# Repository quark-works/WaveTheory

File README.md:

# WaveTheroy

Wireless column staggered PCB compatible with GH60 tray mount cases.

## Features
- 12x4 column staggered board with space for two optional encoders.
- Powered by a e73-2G4M08S1C module, nrf52840 and running ZMK. Firmware available here: [wavetheory-zmk-config](https://github.com/quark-works/wavetheroy-zmk-config).
- Board is in Full HV mode, with a battery of 110 mAh the expected life is around 1 month.
- Has space for a nice!view to show information regarding layers, battery, etc.
- Compatible with GH60 tray mount cases (as pictured).

## More pictures

## This board was prototyped and working, but there are still things to do
- [ ] Add configuration in the firmware for the two encoders.
- [ ] Add configuration in the firmware for the missing compatible layouts.
- [ ] Provide a BOM and POS file for assembly.
- [ ] Fix a bodge wire in the prototype.

## Acknowledgements

Project based off from [Scientist Keyboard](https://github.com/godders/scientist). It uses the same layout based on their reference.

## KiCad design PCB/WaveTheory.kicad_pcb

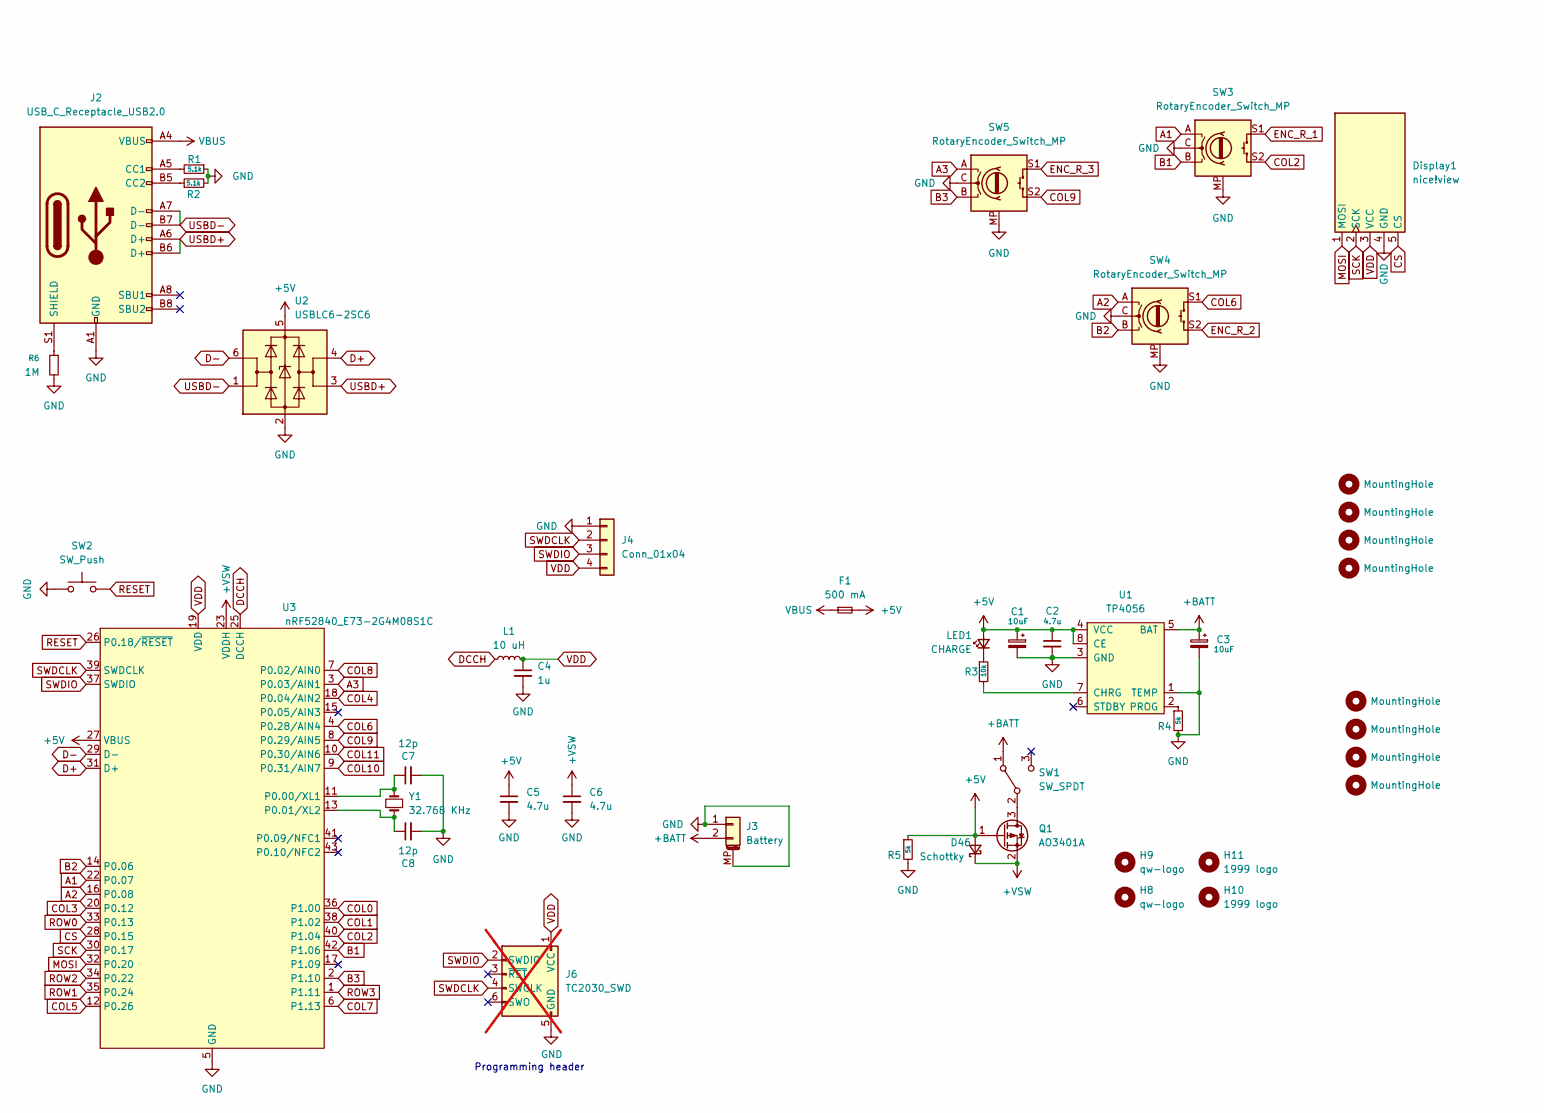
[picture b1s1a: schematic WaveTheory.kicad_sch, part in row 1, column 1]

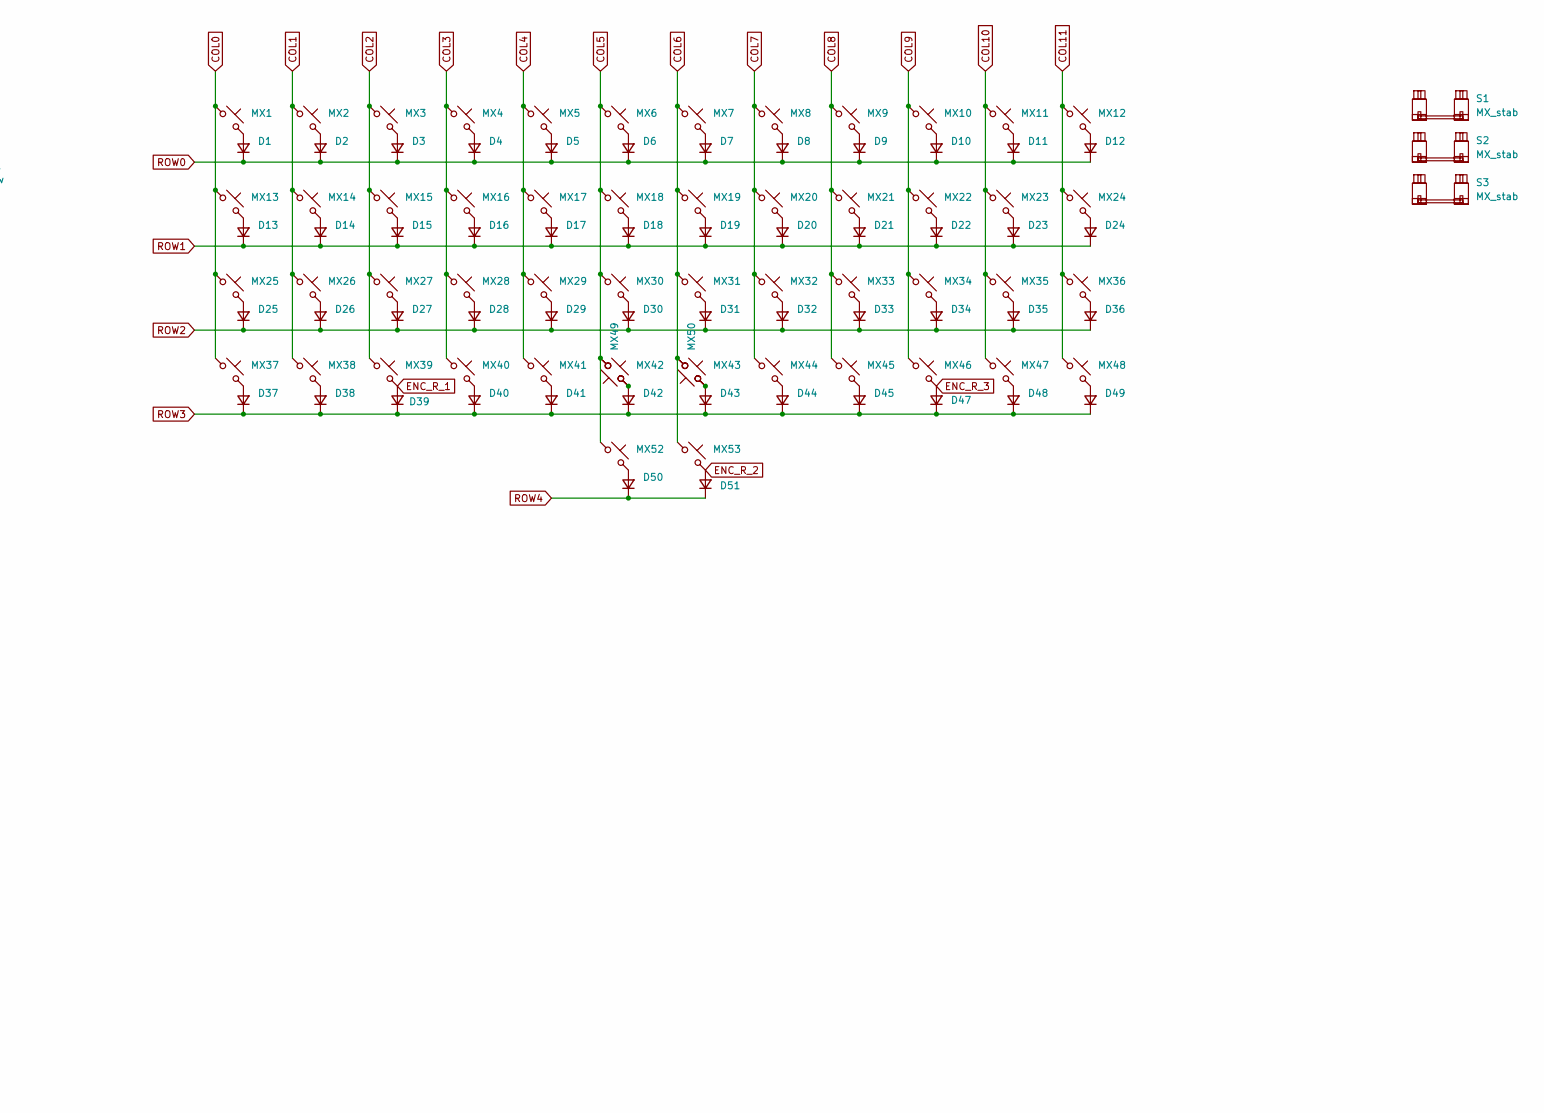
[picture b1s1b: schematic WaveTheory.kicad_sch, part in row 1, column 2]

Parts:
C1, C3: 10uF; CP_EIA-2012-12_Kemet-R
C2, C5, C6: 4.7u; C_0603_1608Metric
C4: 1u; C_0603_1608Metric
C7, C8: 12p; C_0603_1608Metric
D1, D2, D3, D4, D5, D6, D7, D8, D9, D10, D11, D12, D13, D14, D15, D16, D17, D18, D19, D20, D21, D22, D23, D24, D25, D26, D27, D28, D29, D30, D31, D32, D33, D34, D35, D36, D37, D38, D39, D40, D41, D42, D43, D44, D45, D47, D48, D49, D50, D51: 1N4148; CUSTOM D_SOD-123
D46: Schottky; D_0603_1608Metric
Display1: nice!view; nice_view
F1: 500 mA; Fuse_1206_3216Metric
H1, H2, H3, H4: MountingHole; mounting_hole
H5, H6, H7, H12: MountingHole; MountingHole_2.2mm_M2
H8, H9: qw-logo; qw new logo silk + copper sm
H10, H11: 1999 logo; 1999 logo md
J2: USB_C_Receptacle_USB2.0; USB_C_Receptacle_HRO_TYPE-C-31-M-12
J3: Battery; JST_PH_S2B-PH-K_1x02_P2.00mm_Horizontal; LCSC C505023
J4: Conn_01x04; PinHeader_1x04_P2.54mm_Vertical
J6: TC2030_SWD; CON_TC2030_outlined; not fitted
L1: 10 uH; L_0603_1608Metric; LCSC C92982
LED1: CHARGE; LED_0805_2012Metric
MX1, MX2, MX3, MX4, MX5, MX6, MX7, MX8, MX9, MX10, MX11, MX12, MX13, MX14, MX15, MX16, MX17, MX18, MX19, MX20, MX21, MX22, MX23, MX24, MX25, MX26, MX27, MX28, MX29, MX30, MX31, MX32, MX33, MX34, MX35, MX36, MX37, MX38, MX39, MX40, MX41, MX42, MX43, MX44, MX45, MX46, MX47, MX48, MX49, MX50, MX52, MX53: MX_SW_HS; SW_MX_1u
Q1: AO3401A; SOT-23
R1, R2: 5.1k; R_0603_1608Metric
R3: 10k; R_0603_1608Metric
R4, R5: 5k; R_0603_1608Metric
R6: 1M; R_0603_1608Metric
S1, S2, S3: MX_stab; STAB_MX_P_2u
SW1: SW_SPDT; SW_Slide_SPDT_Straight_CK_OS102011MS2Q; LCSC C41430893
SW2: SW_Push; SW_SPST_SKQG_WithStem
SW3, SW4, SW5: RotaryEncoder_Switch_MP; ROT_Alps_EC11E-Switch
U1: TP4056; CustomTP4056; LCSC C16581
U2: USBLC6-2SC6; SOT-23-6
U3: nRF52840_E73-2G4M08S1C; LCSC C356849
Y1: 32.768 KHz; Crystal_SMD_2012-2Pin_2.0x1.2mm; LCSC C55208

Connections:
+5V: C1.1, C2.1, C5.1, D46.2 (A), F1.2, LED1.2 (A), Q1.1 (G), R5.1, U1.4 (VCC), U1.8 (CE), U2.5 (VBUS), U3.27 (VBUS)
+BATT: C3.1, J3.2, SW1.1 (A), U1.5 (BAT)
+VSW: C6.1, D46.1 (K), Q1.2 (S), U3.23 (VDDH)
A1: SW3.A, U3.22 (P0.07)
A2: SW4.A, U3.16 (P0.08)
A3: SW5.A, U3.3 (P0.03/AIN1)
B1: SW3.B, U3.42 (P1.06)
B2: SW4.B, U3.14 (P0.06)
B3: SW5.B, U3.2 (P1.10)
COL0: MX1.2, MX13.2, MX25.2, MX37.2, U3.36 (P1.00)
COL1: MX2.2, MX14.2, MX26.2, MX38.2, U3.38 (P1.02)
COL2: MX3.2, MX15.2, MX27.2, MX39.2, SW3.S2, U3.40 (P1.04)
COL3: MX4.2, MX16.2, MX28.2, MX40.2, U3.20 (P0.12)
COL4: MX5.2, MX17.2, MX29.2, MX41.2, U3.18 (P0.04/AIN2)
COL5: MX6.2, MX18.2, MX30.2, MX42.2, MX49.2, MX52.2, U3.12 (P0.26)
COL6: MX7.2, MX19.2, MX31.2, MX43.2, MX50.2, MX53.2, SW4.S1, U3.4 (P0.28/AIN4)
COL7: MX8.2, MX20.2, MX32.2, MX44.2, U3.6 (P1.13)
COL8: MX9.2, MX21.2, MX33.2, MX45.2, U3.7 (P0.02/AIN0)
COL9: MX10.2, MX22.2, MX34.2, MX46.2, SW5.S2, U3.8 (P0.29/AIN5)
COL10: MX11.2, MX23.2, MX35.2, MX47.2, U3.9 (P0.31/AIN7)
COL11: MX12.2, MX24.2, MX36.2, MX48.2, U3.10 (P0.30/AIN6)
CS: Display1.5 (CS), U3.28 (P0.15)
D+: U2.4 (I/O2), U3.31 (D+)
D-: U2.6 (I/O1), U3.29 (D-)
DCCH: L1.1, U3.25 (DCCH)
ENC_R_1: D39.2 (A), MX39.1, SW3.S1
ENC_R_2: D51.2 (A), MX53.1, SW4.S2
ENC_R_3: D47.2 (A), MX46.1, SW5.S1
GND: C1.2, C2.2, C3.2, C4.2, C5.2, C6.2, C7.2, C8.2, Display1.4 (GND), J2.A1 (GND), J2.A12 (GND), J2.B1 (GND), J2.B12 (GND), J3.1, J3.MP (MountPin), J4.1, J6.5 (GND), R1.1, R2.2, R4.2, R5.2, R6.2, SW2.1, SW3.C, SW3.MP, SW4.C, SW4.MP, SW5.C, SW5.MP, U1.1 (TEMP), U1.3 (GND), U2.2 (GND), U3.5 (GND), U3.21 (GND), U3.24 (GND)
MOSI: Display1.1 (MOSI), U3.32 (P0.20)
unnamed: D1.2 (A), MX1.1
unnamed: D2.2 (A), MX2.1
unnamed: D3.2 (A), MX3.1
unnamed: D4.2 (A), MX4.1
unnamed: D5.2 (A), MX5.1
unnamed: D6.2 (A), MX6.1
unnamed: D7.2 (A), MX7.1
unnamed: D8.2 (A), MX8.1
unnamed: D9.2 (A), MX9.1
unnamed: D10.2 (A), MX10.1
unnamed: D11.2 (A), MX11.1
unnamed: D12.2 (A), MX12.1
unnamed: D13.2 (A), MX13.1
unnamed: D14.2 (A), MX14.1
unnamed: D15.2 (A), MX15.1
unnamed: D16.2 (A), MX16.1
unnamed: D17.2 (A), MX17.1
unnamed: D18.2 (A), MX18.1
unnamed: D19.2 (A), MX19.1
unnamed: D20.2 (A), MX20.1
unnamed: D21.2 (A), MX21.1
unnamed: D22.2 (A), MX22.1
unnamed: D23.2 (A), MX23.1
unnamed: D24.2 (A), MX24.1
unnamed: D25.2 (A), MX25.1
unnamed: D26.2 (A), MX26.1
unnamed: D27.2 (A), MX27.1
unnamed: D28.2 (A), MX28.1
unnamed: D29.2 (A), MX29.1
unnamed: D30.2 (A), MX30.1
unnamed: D31.2 (A), MX31.1
unnamed: D32.2 (A), MX32.1
unnamed: D33.2 (A), MX33.1
unnamed: D34.2 (A), MX34.1
unnamed: D35.2 (A), MX35.1
unnamed: D36.2 (A), MX36.1
unnamed: D37.2 (A), MX37.1
unnamed: D38.2 (A), MX38.1
unnamed: D40.2 (A), MX40.1
unnamed: D41.2 (A), MX41.1
unnamed: D42.2 (A), MX42.1, MX49.1
unnamed: D43.2 (A), MX43.1, MX50.1
unnamed: D44.2 (A), MX44.1
unnamed: D45.2 (A), MX45.1
unnamed: D48.2 (A), MX47.1
unnamed: D49.2 (A), MX48.1
unnamed: D50.2 (A), MX52.1
unnamed: J2.A5 (CC1), R1.2
unnamed: J2.B5 (CC2), R2.1
unnamed: J2.S1 (SHIELD), R6.1
unnamed: LED1.1 (K), R3.1
unnamed: Q1.3 (D), SW1.2 (B)
unnamed: R3.2, U1.7 (CHRG)
unnamed: R4.1, U1.2 (PROG)
unnamed: C7.1, U3.11 (P0.00/XL1), Y1.2
unnamed: C8.1, U3.13 (P0.01/XL2), Y1.1
RESET: SW2.2, U3.26 (P0.18/~RESET)
ROW0: D1.1 (K), D2.1 (K), D3.1 (K), D4.1 (K), D5.1 (K), D6.1 (K), D7.1 (K), D8.1 (K), D9.1 (K), D10.1 (K), D11.1 (K), D12.1 (K), U3.33 (P0.13)
ROW1: D13.1 (K), D14.1 (K), D15.1 (K), D16.1 (K), D17.1 (K), D18.1 (K), D19.1 (K), D20.1 (K), D21.1 (K), D22.1 (K), D23.1 (K), D24.1 (K), U3.35 (P0.24)
ROW2: D25.1 (K), D26.1 (K), D27.1 (K), D28.1 (K), D29.1 (K), D30.1 (K), D31.1 (K), D32.1 (K), D33.1 (K), D34.1 (K), D35.1 (K), D36.1 (K), U3.34 (P0.22)
ROW3: D37.1 (K), D38.1 (K), D39.1 (K), D40.1 (K), D41.1 (K), D42.1 (K), D43.1 (K), D44.1 (K), D45.1 (K), D47.1 (K), D48.1 (K), D49.1 (K), U3.1 (P1.11)
ROW4: D50.1 (K), D51.1 (K)
SCK: Display1.2 (SCK), U3.30 (P0.17)
SWDCLK: J4.2, J6.4 (SWCLK), U3.39 (SWDCLK)
SWDIO: J4.3, J6.2 (SWDIO), U3.37 (SWDIO)
USBD+: J2.A6 (D+), J2.B6 (D+), U2.3 (I/O2)
USBD-: J2.A7 (D-), J2.B7 (D-), U2.1 (I/O1)
VBUS: F1.1, J2.A4 (VBUS), J2.A9 (VBUS), J2.B4 (VBUS), J2.B9 (VBUS)
VDD: C4.1, Display1.3 (VCC), J4.4, J6.1 (VCC), L1.2, U3.19 (VDD)

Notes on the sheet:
Programming header

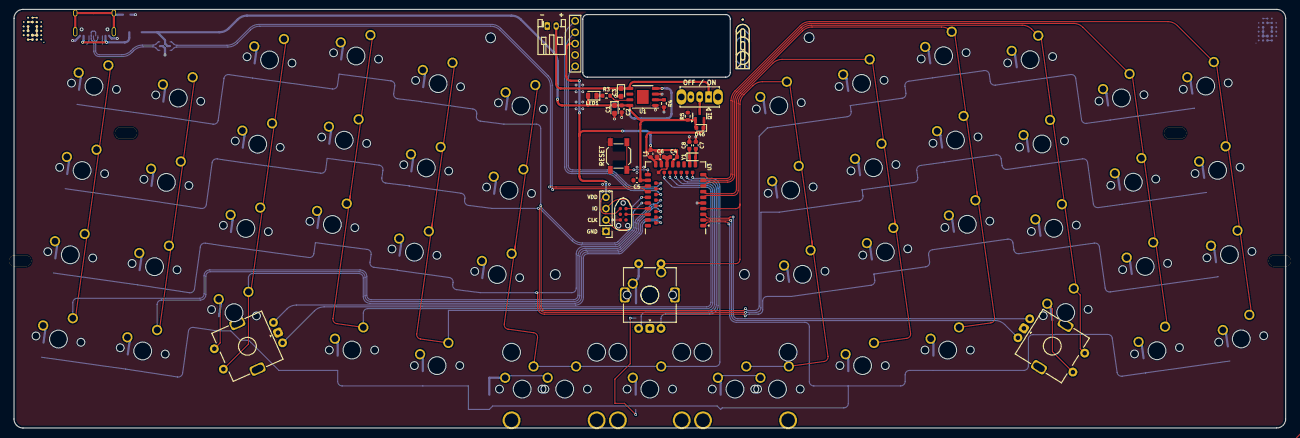
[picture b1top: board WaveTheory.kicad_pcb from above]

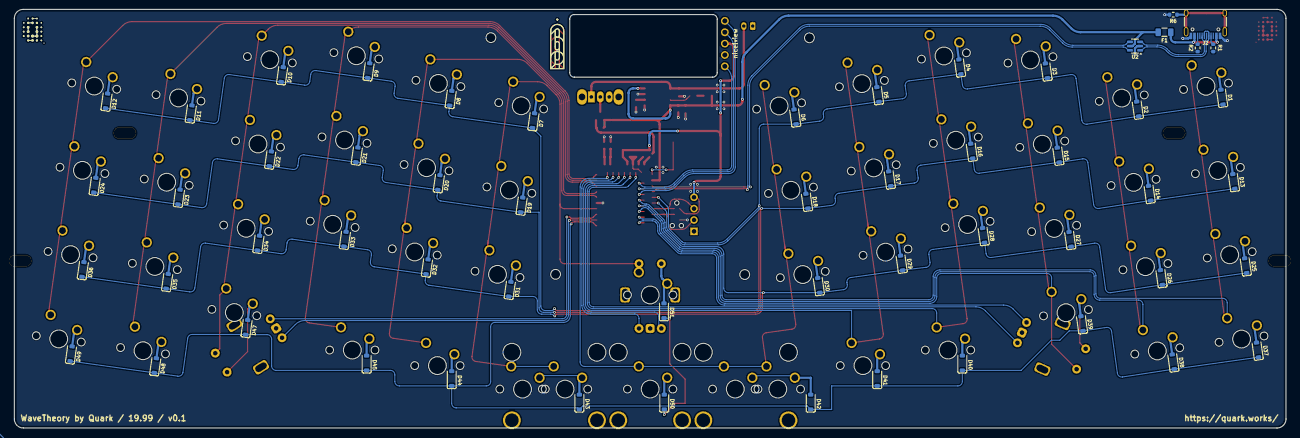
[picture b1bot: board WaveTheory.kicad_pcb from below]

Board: 2 copper layers, 284.6 x 93.7 mm, 150 parts (58 on the bottom side), 99 nets.

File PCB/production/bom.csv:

Designator,Footprint,Quantity,Value,LCSC Part #
"C1, C3",CP_EIA-2012-12_Kemet-R,2,10uF,
"C2, C5, C6",0603,3,4.7u,
C4,0603,1,1u,
"C7, C8",0603,2,12p,
"D1, D10, D11, D12, D13, D14, D15, D16, D17, D18, D19, D2, D20, D21, D22, D23, D24, D25, D26, D27, D28, D29, D3, D30, D31, D32, D33, D34, D35, D36, D37, D38, D39, D4, D40, D41, D42, D43, D44, D45, D47, D48, D49, D5, D50, D51, D6, D7, D8, D9",CUSTOM D_SOD-123,50,1N4148,
D46,0603,1,Schottky,
DISPLAY1,nice_view,1,nice!view,
F1,1206,1,500 mA,
J2,USB_C_Receptacle_HRO_TYPE-C-31-M-12,1,USB_C_Receptacle_USB2.0,
J3,JST_PH_S2B-PH-K_1x02_P2.00mm_Horizontal,1,Battery,C505023
L1,0603,1,10 uH,C92982
LED1,0805,1,CHARGE,
"MX1, MX10, MX11, MX12, MX13, MX14, MX15, MX16, MX17, MX18, MX19, MX2, MX20, MX21, MX22, MX23, MX24, MX25, MX26, MX27, MX28, MX29, MX3, MX30, MX31, MX32, MX33, MX34, MX35, MX36, MX37, MX38, MX39, MX4, MX40, MX41, MX42, MX43, MX44, MX45, MX46, MX47, MX48, MX49, MX5, MX50, MX52, MX53, MX6, MX7, MX8, MX9",SW_MX_1u,52,MX_SW_HS,
Q1,SOT-23,1,AO3401A,
"R1, R2",0603,2,5.1k,
R3,0603,1,10k,
"R4, R5",0603,2,5k,
R6,0603,1,1M,
"S1, S2, S3",STAB_MX_P_2u,3,MX_stab,
SW1,SW_Slide_SPDT_Straight_CK_OS102011MS2Q,1,SW_SPDT,C41430893
SW2,SW_SPST_SKQG_WithStem,1,SW_Push,
"SW3, SW4, SW5",ROT_Alps_EC11E-Switch,3,RotaryEncoder_Switch_MP,
U1,CustomTP4056,1,TP4056,C16581
U2,SOT-23-6,1,USBLC6-2SC6,
U3,nRF52840_E73-2G4M08S1C,1,nRF52840_E73-2G4M08S1C,C356849
Y1,Crystal_SMD_2012-2Pin_2.0x1.2mm,1,32.768 KHz,C55208

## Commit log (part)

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2025-12-23 First commit!
2026-03-24 First revision
2026-03-24 added original reference
